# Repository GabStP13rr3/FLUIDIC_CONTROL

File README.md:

# FLUIDIC_CONTROL

User interface for microfluidic pumping system. Further information about the hardware behind the project can be found by following one of the link provided below:
- [Hackster Project Documentation](https://www.hackster.io/gabrielstpierre02/programmable-fluidic-pumping-system-58efa4)
- [Instructable Project Documentation](https://www.instructables.com/MicroFluidic-Pumping-System/)
- [Fusion 360 Project Page](https://gallery.autodesk.com/projects/164220/microfluidic-pumping-system)
- [Software Interface Testing](https://www.youtube.com/watch?v=qG9HOkH4AtU)

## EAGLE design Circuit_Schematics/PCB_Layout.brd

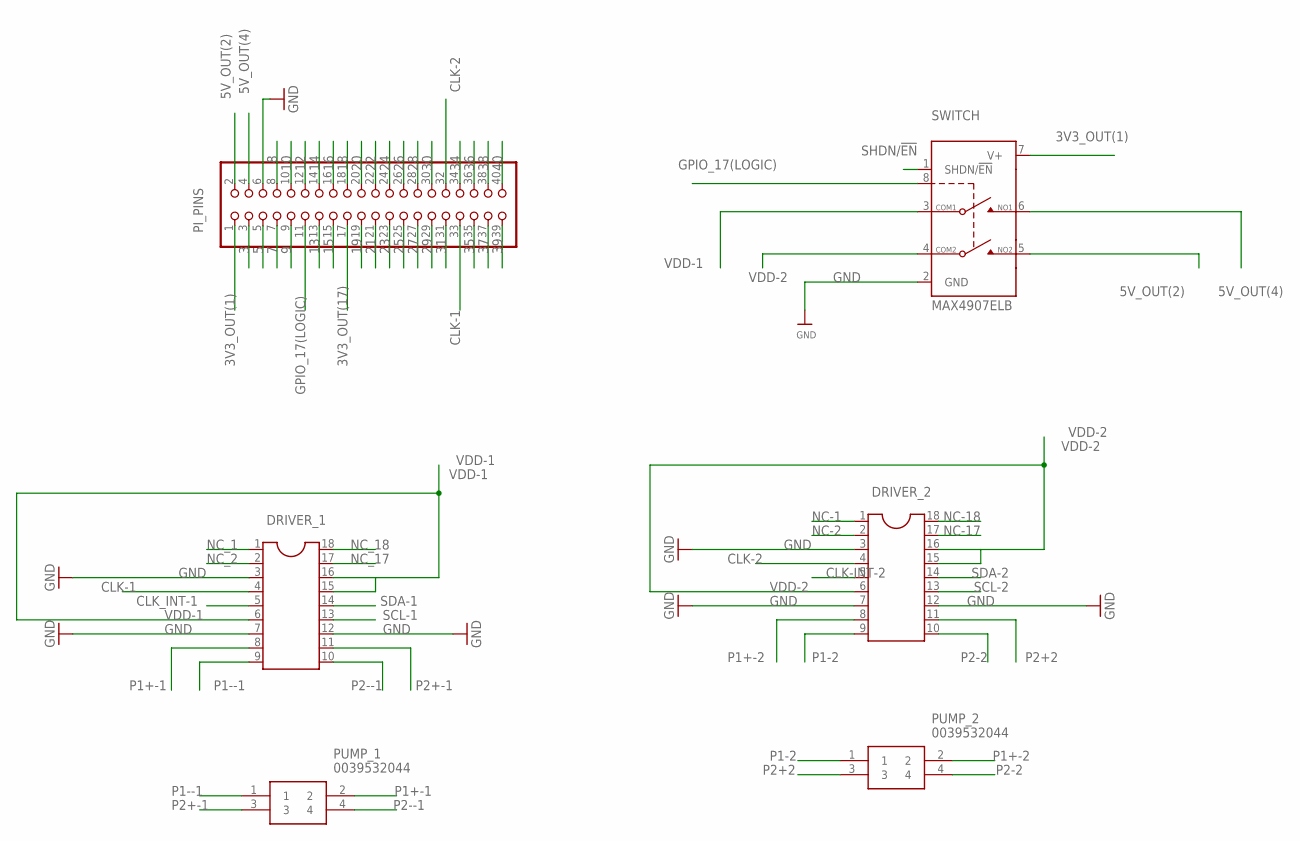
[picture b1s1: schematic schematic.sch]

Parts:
DRIVER_1, DRIVER_2: DIL18
PI_PINS: PINHD-2X20; 2X20
PUMP_1, PUMP_2: 0039532044
SWITCH: MAX4907ELB; UDFN8

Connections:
3: PI_PINS.3
3V3_OUT(1): PI_PINS.1, SWITCH.7 (V+)
3V3_OUT(17): PI_PINS.17
5: PI_PINS.5
5V_OUT(2): PI_PINS.2, SWITCH.5 (NO2)
5V_OUT(4): PI_PINS.4, SWITCH.6 (NO1)
7: PI_PINS.7
8: PI_PINS.8
9: PI_PINS.9
10: PI_PINS.10
12: PI_PINS.12
13: PI_PINS.13
14: PI_PINS.14
15: PI_PINS.15
16: PI_PINS.16
18: PI_PINS.18
19: PI_PINS.19
20: PI_PINS.20
21: PI_PINS.21
22: PI_PINS.22
23: PI_PINS.23
24: PI_PINS.24
25: PI_PINS.25
26: PI_PINS.26
27: PI_PINS.27
28: PI_PINS.28
29: PI_PINS.29
30: PI_PINS.30
31: PI_PINS.31
34: PI_PINS.34
35: PI_PINS.35
36: PI_PINS.36
37: PI_PINS.37
38: PI_PINS.38
39: PI_PINS.39
40: PI_PINS.40
CLK-1: DRIVER_1.4, PI_PINS.33
CLK-2: DRIVER_2.4, PI_PINS.32
CLK-INT-2: DRIVER_2.5
CLK_INT-1: DRIVER_1.5
GND: DRIVER_1.3, DRIVER_1.7, DRIVER_1.12, DRIVER_2.3, DRIVER_2.7, DRIVER_2.12, PI_PINS.6, SWITCH.2 (GND)
GPIO_17(LOGIC): PI_PINS.11, SWITCH.8 (IN)
NC-1: DRIVER_2.1
NC-2: DRIVER_2.2
NC-17: DRIVER_2.17
NC-18: DRIVER_2.18
NC_1: DRIVER_1.1
NC_2: DRIVER_1.2
NC_17: DRIVER_1.17
NC_18: DRIVER_1.18
P1+-1: DRIVER_1.8, PUMP_1.2
P1+-2: DRIVER_2.8, PUMP_2.2
P1-2: DRIVER_2.9, PUMP_2.1
P1--1: DRIVER_1.9, PUMP_1.1
P2+2: DRIVER_2.11, PUMP_2.3
P2+-1: DRIVER_1.11, PUMP_1.3
P2-2: DRIVER_2.10, PUMP_2.4
P2--1: DRIVER_1.10, PUMP_1.4
SCL-1: DRIVER_1.13
SCL-2: DRIVER_2.13
SDA-1: DRIVER_1.14
SDA-2: DRIVER_2.14
SHDN/!EN: SWITCH.1 (SHDN/!EN)
VDD-1: DRIVER_1.6, DRIVER_1.15, DRIVER_1.16, SWITCH.3 (COM1)
VDD-2: DRIVER_2.6, DRIVER_2.15, DRIVER_2.16, SWITCH.4 (COM2)

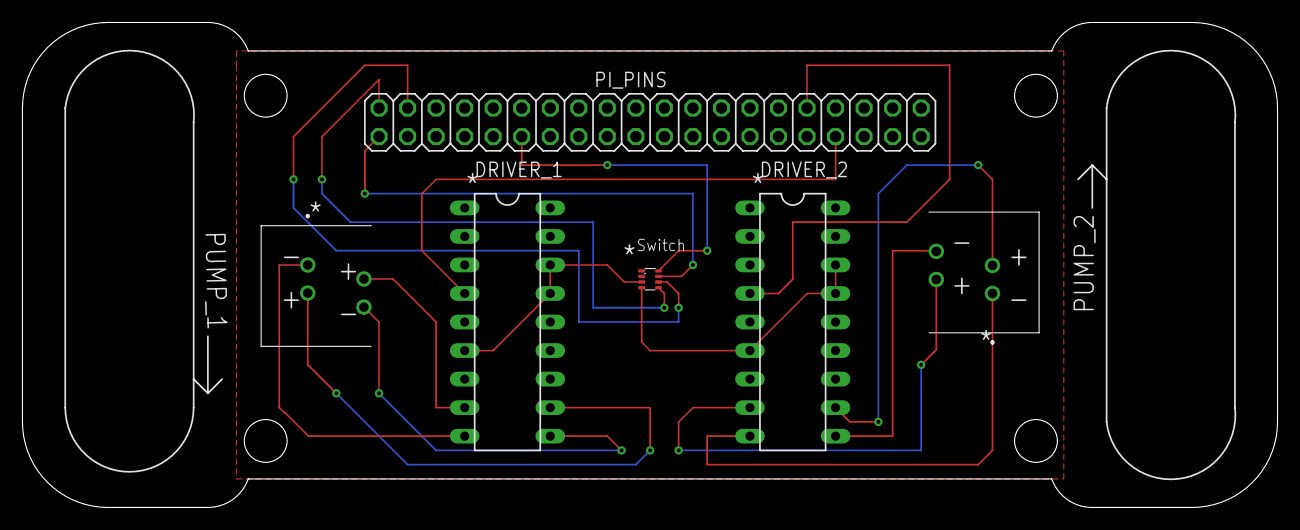
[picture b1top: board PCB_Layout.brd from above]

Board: 2 copper layers, 111.7 x 43.2 mm, 6 parts (0 on the bottom side), 17 nets.
